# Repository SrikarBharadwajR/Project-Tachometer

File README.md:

# Project-Tachometer
Instrument which is used for measuring rotations per minute of a rotating object.

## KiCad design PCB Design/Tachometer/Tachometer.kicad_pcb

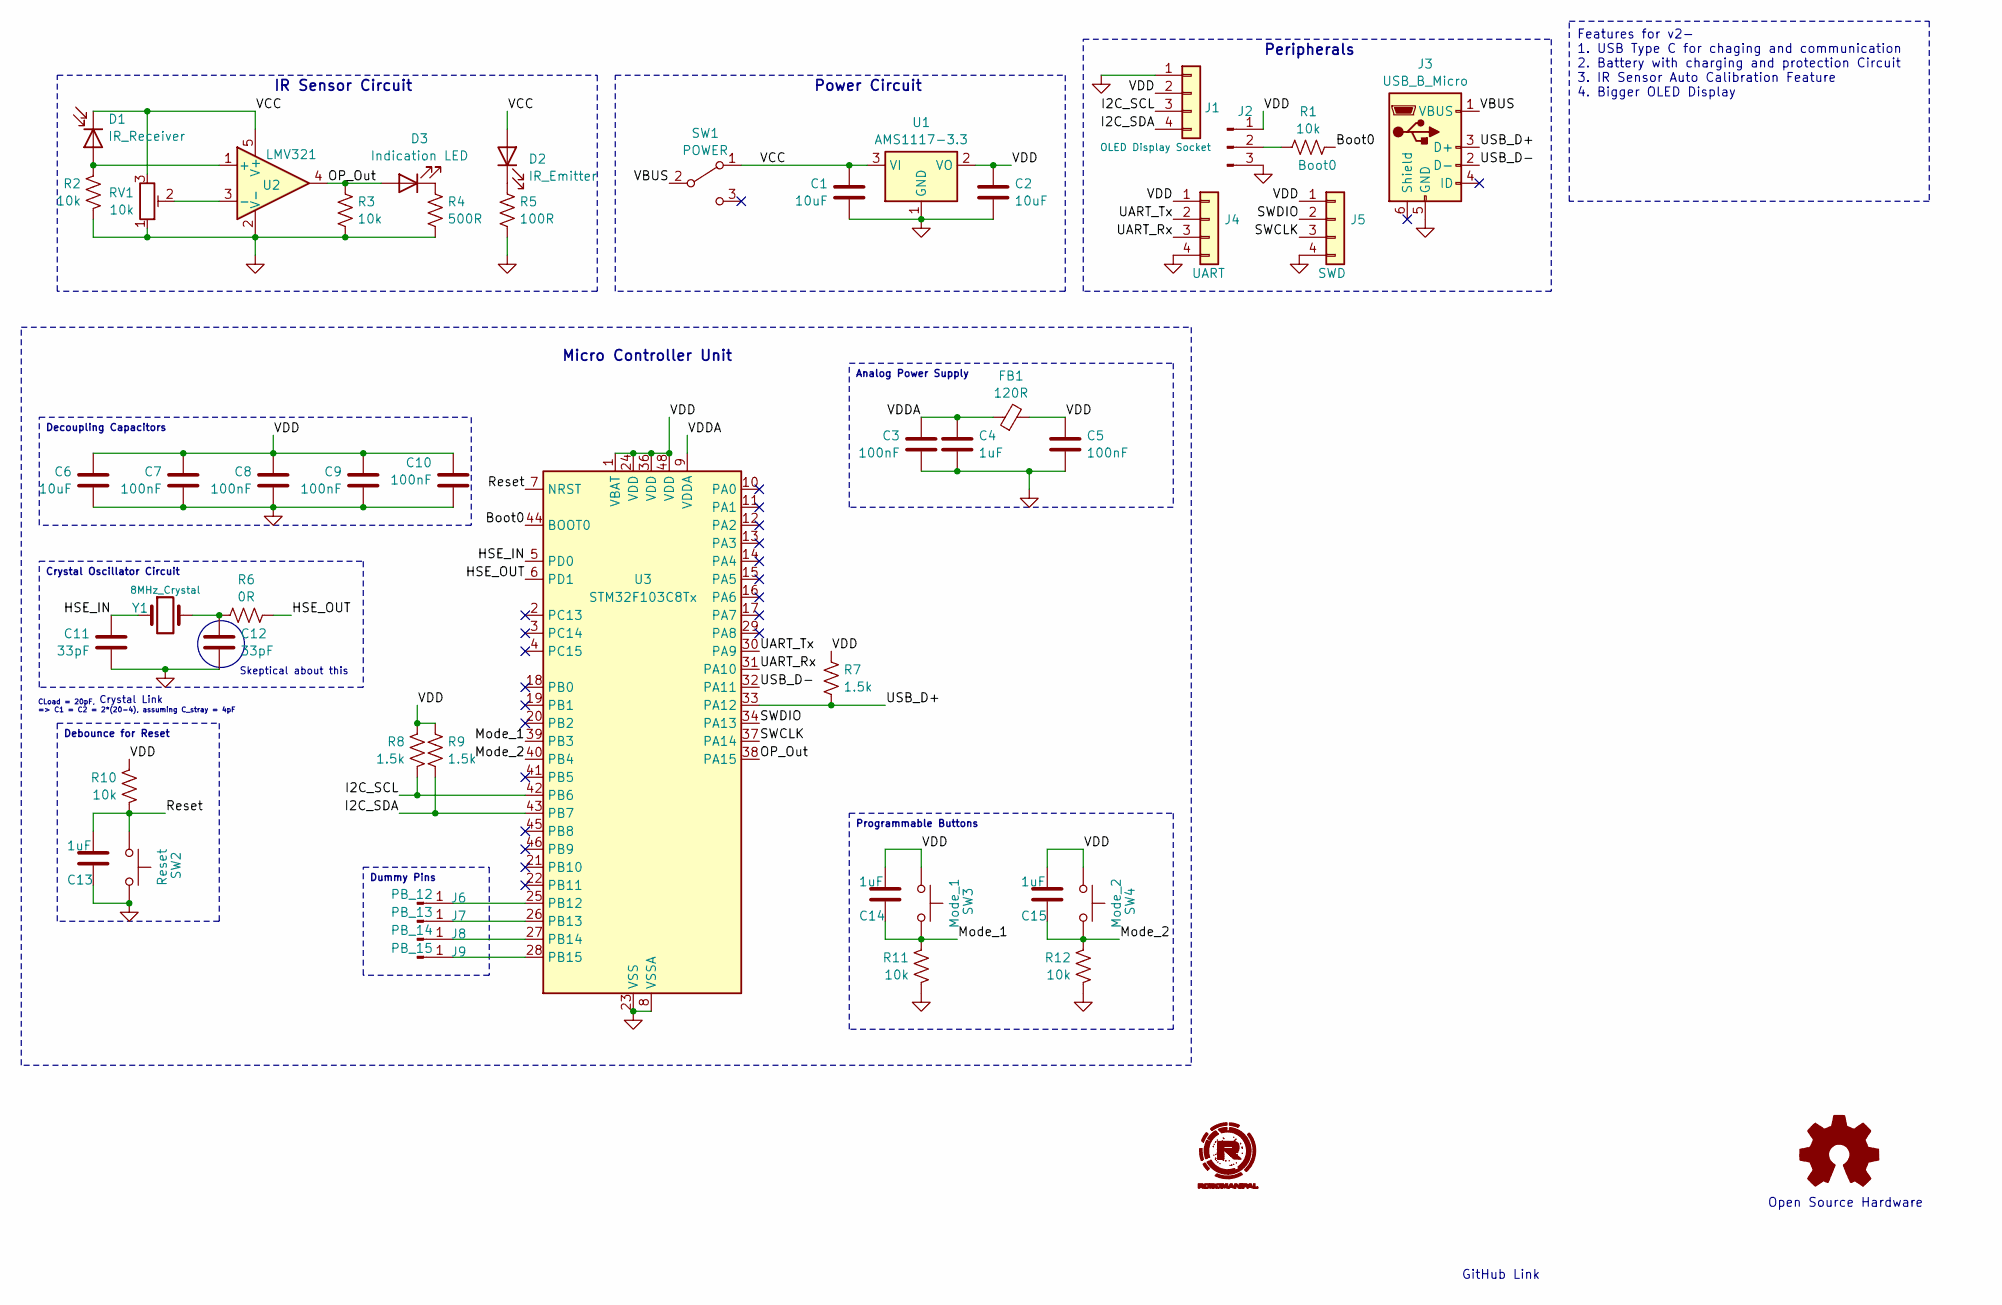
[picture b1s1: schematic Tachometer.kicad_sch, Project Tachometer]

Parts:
C1, C2, C6: 10uF; C_0805_2012Metric_Pad1.18x1.45mm_HandSolder
C3, C5, C7, C8, C9, C10: 100nF; C_0805_2012Metric_Pad1.18x1.45mm_HandSolder
C4, C13, C14, C15: 1uF; C_0805_2012Metric_Pad1.18x1.45mm_HandSolder
C11, C12: 33pF; C_0805_2012Metric_Pad1.18x1.45mm_HandSolder
D1: IR_Receiver; LED_5mm_Radial
D2: IR_Emitter; LED_5mm_Radial
D3: Indication LED; LED_0603_1608Metric_Pad1.05x0.95mm_HandSolder
FB1: 120R; L_0603_1608Metric_Pad1.05x0.95mm_HandSolder
J1: OLED Display Socket; PinSocket_1x04_P2.54mm_Vertical
J2: Boot0; PinHeader_1x03_P2.54mm_Vertical
J3: USB_B_Micro; USB_Micro-B_GCT_USB3076-30-A
J4: UART; PinHeader_1x04_P2.54mm_Vertical
J5: SWD; PinHeader_1x04_P2.54mm_Vertical
J6: PB_12; SolderWirePad_1x01_SMD_1x2mm
J7: PB_13; SolderWirePad_1x01_SMD_1x2mm
J8: PB_14; SolderWirePad_1x01_SMD_1x2mm
J9: PB_15; SolderWirePad_1x01_SMD_1x2mm
R1, R2, R3, R10, R11, R12: 10k; R_0603_1608Metric_Pad0.98x0.95mm_HandSolder
R4: 500R; R_0603_1608Metric_Pad0.98x0.95mm_HandSolder
R5: 100R; R_Axial_DIN0204_L3.6mm_D1.6mm_P5.08mm_Horizontal
R6: 0R; R_0603_1608Metric_Pad0.98x0.95mm_HandSolder
R7, R8, R9: 1.5k; R_0603_1608Metric_Pad0.98x0.95mm_HandSolder
RV1: 10k; Potentiometer_Bourns_3296W_Vertical
SW1: POWER; SW_SPDT_PCM12
SW2: Reset; SW_TS09-63-25-WT-160-SMT-TR
SW3: Mode_1; SW_TS09-63-25-WT-160-SMT-TR
SW4: Mode_2; SW_TS09-63-25-WT-160-SMT-TR
U1: AMS1117-3.3; SOT-223-3_TabPin2
U2: LMV321; SOT25
U3: STM32F103C8Tx; LQFP-48_7x7mm_P0.5mm
Y1: 8MHz_Crystal; Crystal_SMD_HC49-SD

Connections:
/Boot0: R1.2, U3.44 (BOOT0)
/HSE_IN: C11.1, U3.5 (PD0), Y1.1
/HSE_OUT: R6.2, U3.6 (PD1)
/I2C_SCL: J1.3, R8.1, U3.42 (PB6)
/I2C_SDA: J1.4, R9.1, U3.43 (PB7)
/Mode_1: C14.1, R11.2, SW3.2, U3.39 (PB3)
/Mode_2: C15.1, R12.2, SW4.2, U3.40 (PB4)
/OP_Out: D3.2 (A), R3.1, U2.4, U3.38 (PA15)
/Reset: C13.2, R10.1, SW2.1, U3.7 (NRST)
/SWCLK: J5.3, U3.37 (PA14)
/SWDIO: J5.2, U3.34 (PA13)
/UART_Rx: J4.3, U3.31 (PA10)
/UART_Tx: J4.2, U3.30 (PA9)
/USB_D+: J3.3 (D+), R7.1, U3.33 (PA12)
/USB_D-: J3.2 (D-), U3.32 (PA11)
/VBUS: J3.1 (VBUS), SW1.2 (B)
/VCC: C1.1, D1.1 (K), D2.2 (A), RV1.3, SW1.1 (A), U1.3 (VI), U2.5 (V+)
/VDD: C2.1, C5.1, C6.1, C7.1, C8.1, C9.1, C10.1, C14.2, C15.2, FB1.2, J1.2, J2.1, J4.1, J5.1, R7.2, R8.2, R9.2, R10.2, SW3.1, SW4.1, U1.2 (VO), U3.1 (VBAT), U3.24 (VDD), U3.36 (VDD), U3.48 (VDD)
/VDDA: C3.1, C4.1, FB1.1, U3.9 (VDDA)
GND: C1.2, C2.2, C3.2, C4.2, C5.2, C6.2, C7.2, C8.2, C9.2, C10.2, C11.2, C12.2, C13.1, J1.1, J2.3, J3.5 (GND), J4.4, J5.4, R2.2, R3.2, R4.2, R5.2, R11.1, R12.1, RV1.1, SW2.2, U1.1 (GND), U2.2 (V-), U3.8 (VSSA), U3.23 (VSS), U3.35 (VSS), U3.47 (VSS)
unnamed: C12.1, R6.1, Y1.2
unnamed: D1.2 (A), R2.1, U2.1 (+)
unnamed: D2.1 (K), R5.1
unnamed: D3.1 (K), R4.1
unnamed: J2.2, R1.1
unnamed: J6.1, U3.25 (PB12)
unnamed: J7.1, U3.26 (PB13)
unnamed: J8.1, U3.27 (PB14)
unnamed: J9.1, U3.28 (PB15)
unnamed: RV1.2, U2.3 (-)

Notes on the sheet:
Analog Power Supply
Decoupling Capacitors
Crystal Oscillator Circuit
Dummy Pins
Programmable Buttons
Debounce for Reset
Features for v2- 1. USB Type C for chaging and communication 2. Battery with charging and protection Circuit 3. IR Sensor Auto Calibration Feature 4. Bigger OLED Display
Peripherals
Skeptical about this
Power Circuit
CLoad = 20pF, => C1 = C2 = 2*(20-4), assuming C_stray = 4pF
Micro Controller Unit
GitHub Link
Crystal Link
Open Source Hardware
IR Sensor Circuit

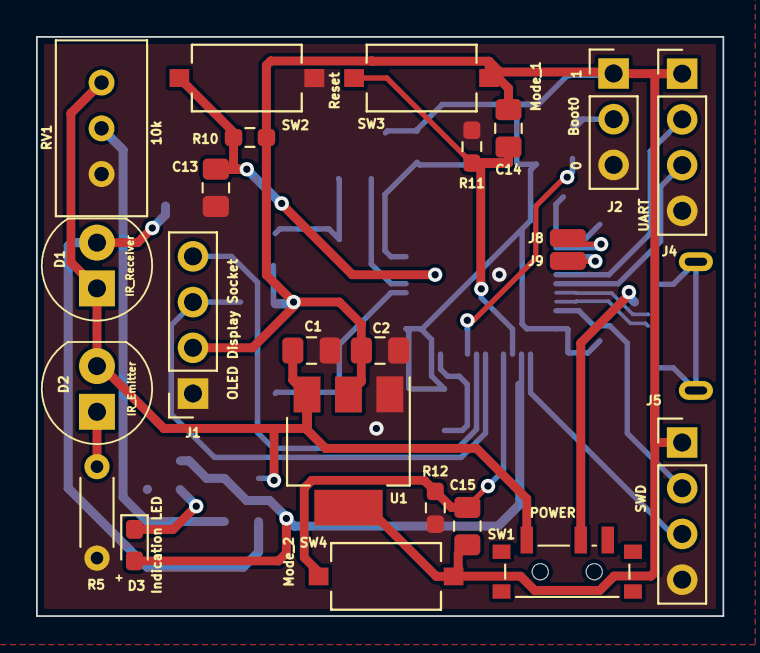
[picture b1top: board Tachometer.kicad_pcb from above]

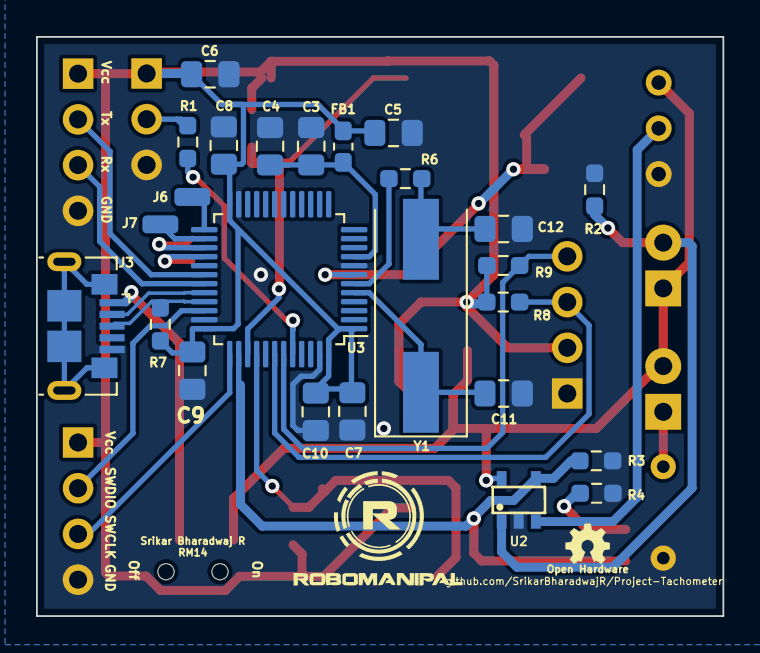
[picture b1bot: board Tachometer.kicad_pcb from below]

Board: 2 copper layers, 38.1 x 32.2 mm, 50 parts (26 on the bottom side), 30 nets.

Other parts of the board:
Ref**: Val**; OSHW_Logo_2.5mm

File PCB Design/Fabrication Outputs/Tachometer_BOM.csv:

Item,Quantity,Reference,Value,Footprint,Manufacturer Part Number,Manfacturer Name,Distributor Part Number,Description
1,3,"SW2,SW3,SW4",-,SW_TS09-63-25-WT-160-SMT-TR,TS09-63-25-WT-160-SMT-TR,CUI Devices,2223-TS09-63-25-WT-160-SMT-TRCT-ND,Tactile Switch SPST-NO Top Actuated Surface Mount
2,4,"C13,C15,C14,C4",1uF,C_0805_2012Metric_Pad1.18x1.45mm_HandSolder,GCG21BR71H105KA01L,Murata Electronics,490-GCG21BR71H105KA01LCT-ND,1 µF ±10% 50V Ceramic Capacitor X7R 0805 (2012 Metric)
3,3,"C1,C2,C6",10uF,C_0805_2012Metric_Pad1.18x1.45mm_HandSolder,GRM21BR61E106KA73L,Murata Electronics,490-5523-1-ND,10 µF ±10% 25V Ceramic Capacitor X5R 0805 (2012 Metric)
4,6,"R11,R10,R12,R1,R2,R3",10k,R_0603_1608Metric_Pad0.98x0.95mm_HandSolder,ESR03EZPF1002,Rohm Semiconductor,RHM10KADCT-ND,"10 kOhms ±1% 0.25W, 1/4W Chip Resistor 0603 (1608 Metric) Automotive AEC-Q200, Pulse Withstanding Thick Film"
5,1,SW1,POWER,SW_SPDT_PCM12,PCM12SMTR,C&K,401-2016-1-ND,"Slide Switch SPDT Surface Mount, Right Angle"
6,1,U1,AMS1117-3.3,SOT-223-3_TabPin2,AZ1117H-3.3TRE1,Diodes Incorporated,AZ1117H-3.3TRE1DICT-ND,Linear Voltage Regulator IC Positive Fixed 1 Output 1A SOT-223-3
7,1,D3,Indication LED,LED_0603_1608Metric_Pad1.05x0.95mm_HandSolder,5988070107F,Dialight,350-2035-1-ND,Green 568nm LED Indication - Discrete 2V 0603 (1608 Metric)
8,6,"C7,C8,C9,C10,C5,C3",100nF,C_0805_2012Metric_Pad1.18x1.45mm_HandSolder,GCJ21BR72A104KA01K,Murata Electronics,490-GCJ21BR72A104KA01KCT-ND,0.1 µF ±10% 100V Ceramic Capacitor X7R 0805 (2012 Metric)
9,1,Y1,8MHz_Crystal,Crystal_SMD_HC49-SD,FC4SDCBMF8.0-T1,Fox Electronics,631-1010-1-ND,8 MHz ±30ppm Crystal 20pF 80 Ohms HC-49/US
10,3,"R9,R8,R7",1.5k,R_0603_1608Metric_Pad0.98x0.95mm_HandSolder,ESR03EZPF1501,Rohm Semiconductor,RHM1.50KADCT-ND,"1.5 kOhms ±1% 0.25W, 1/4W Chip Resistor 0603 (1608 Metric) Automotive AEC-Q200, Pulse Withstanding Thick Film"
11,1,J3,USB_B_Micro,USB_Micro-B_GCT_USB3076-30-A,USB3076-30-A,GCT,2073-USB3076-30-ACT-ND,"USB - micro B USB 2.0 Receptacle Connector 5 Position Surface Mount, Right Angle; Through Hole"
12,1,R4,500R,R_0603_1608Metric_Pad0.98x0.95mm_HandSolder,ESR03EZPJ511,Rohm Semiconductor,RHM510DCT-ND,"510 Ohms ±5% 0.25W, 1/4W Chip Resistor 0603 (1608 Metric) Automotive AEC-Q200, Pulse Withstanding Thick Film"
13,1,U3,STM32F103C8Tx,LQFP-48_7x7mm_P0.5mm,STM32F103C8T6TR,STMicroelectronics,497-17666-1-ND,ARM® Cortex®-M3 STM32F1 Microcontroller IC 32-Bit Single-Core 72MHz 64KB (64K x 8) FLASH 48-LQFP (7x7)
14,1,U2,LMV321,SOT25,LMV321WG-7,Diodes Incorporated,LMV321WG-7DICT-ND,General Purpose Amplifier 1 Circuit Rail-to-Rail SOT-25
15,1,FB1,120R,L_0603_1608Metric_Pad1.05x0.95mm_HandSolder,MI0603M121R-10,Laird-Signal Integrity Products,240-2375-1-ND,"120 Ohms @ 100 MHz 1 Power, Signal Line Ferrite Bead 0603 (1608 Metric) 2A 50mOhm"
16,2,"C11,C12",33pF,C_0805_2012Metric_Pad1.18x1.45mm_HandSolder,GQM2195C2E330FB12D,Murata Electronics,490-GQM2195C2E330FB12DCT-ND,"33 pF ±1% 250V Ceramic Capacitor C0G, NP0 0805 (2012 Metric)"
17,1,R6,0R,R_0603_1608Metric_Pad0.98x0.95mm_HandSolder,SFR03EZPJ000,Rohm Semiconductor,511-1823-1-ND,0 Ohms Jumper Chip Resistor 0603 (1608 Metric) Anti-Sulfur Thick Film

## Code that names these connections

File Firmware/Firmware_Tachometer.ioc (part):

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Mcu.Name=STM32F103C(8-B)Tx
Mcu.Package=LQFP48
Mcu.UserName=STM32F103C8Tx
PA10.Mode=Asynchronous
PA10.Signal=USART1_RX
PA11.Mode=Device
PA11.Signal=USB_DM
PA12.Mode=Device
PA12.Signal=USB_DP
PA13.Mode=Serial_Wire
PA13.Signal=SYS_JTMS-SWDIO
PA14.Mode=Serial_Wire
PA14.Signal=SYS_JTCK-SWCLK
PA15.Signal=S_TIM2_CH1_ETR
PA9.Mode=Asynchronous
PA9.Signal=USART1_TX
PB6.Mode=I2C
PB6.Signal=I2C1_SCL
PB7.Mode=I2C
PB7.Signal=I2C1_SDA
PD0-OSC_IN.Mode=HSE-External-Oscillator
PD0-OSC_IN.Signal=RCC_OSC_IN
PD1-OSC_OUT.Mode=HSE-External-Oscillator
PD1-OSC_OUT.Signal=RCC_OSC_OUT
RCC.SYSCLKFreq_VALUE=72000000
RCC.SYSCLKSource=RCC_SYSCLKSOURCE_PLLCLK
board=custom

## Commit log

2023-09-03 Firmware Updated
2023-09-03 KiCad
2023-09-06 Schematic
2023-09-08 Schematic_Update
2023-09-09 PCB_Routed
2023-09-10 Routed
2023-09-17 Fabrications Updated
2023-09-17 Gerber
